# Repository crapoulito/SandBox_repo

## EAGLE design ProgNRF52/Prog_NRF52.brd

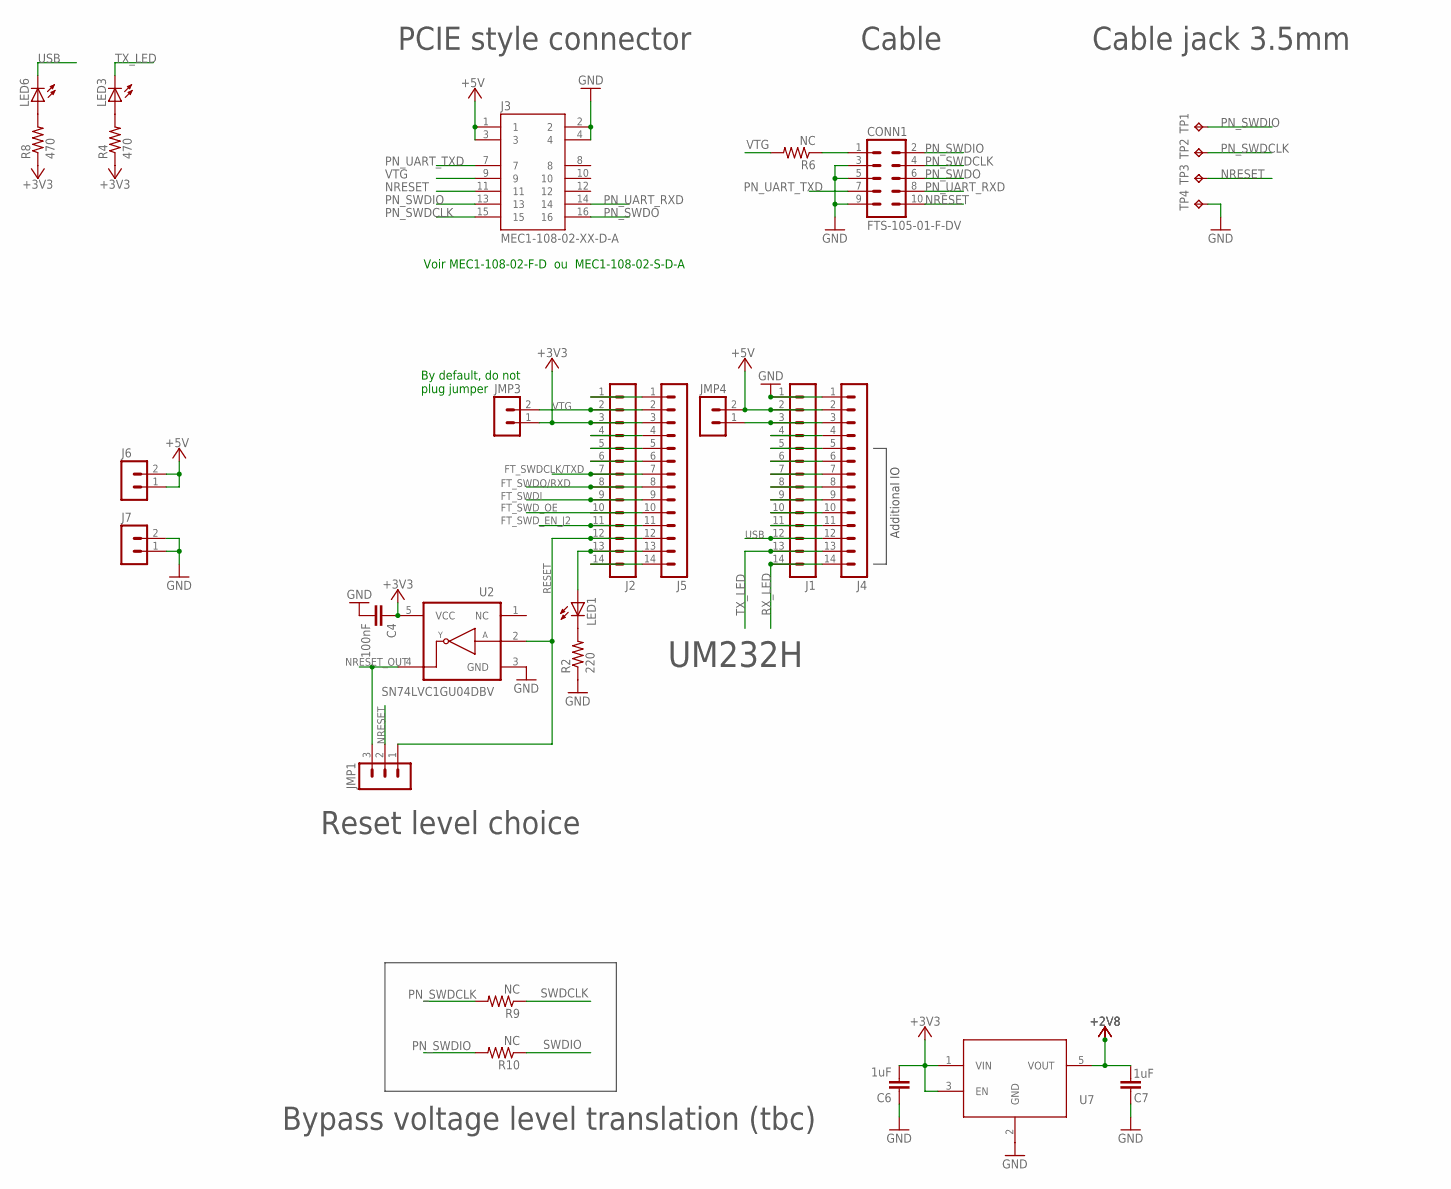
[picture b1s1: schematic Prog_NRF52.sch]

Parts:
C4: 100nF; C0603K
C6, C7: 1uF; C0603K
CONN1: FTS-105-01-F-DV
J1, J2, J4, J5: MA14-1
J3: MEC1-108-02-XX-D-A
J6, J7: MA02-1
JMP1: MA03-1
JMP3, JMP4: MA02-1
LED1, LED3, LED6: LEDCHIP-LED0603; CHIP-LED0603
R2: 220; R0603
R4, R8: 470; R0603
R6, R9, R10: NC; R0603
TP1, TP2, TP3, TP4: TPPAD1-13; P1-13
U2: SN74LVC1GU04DBV; SOT23-5
U7: NCP114ASN280T1G; SOT23-5

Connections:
+2V8: C7.2, U7.5 (VOUT)
+3V3: C4.1, C6.2, J2.3, J5.3, JMP3.1, R4.1, R8.1, U2.5 (VCC), U7.1 (VIN), U7.3 (EN)
+5V: J1.2, J3.1, J3.3, J4.2, J6.1, J6.2, JMP4.2
FT_SWDCLK/TXD: J2.7, J5.7
FT_SWDI: J2.9, J5.9
FT_SWDO/RXD: J2.8, J5.8
FT_SWD_EN_J2: J2.11, J5.11
FT_SWD_OE: J2.10, J5.10
GND: C4.2, C6.1, C7.1, CONN1.3, CONN1.5, CONN1.9, J1.1, J3.2, J3.4, J4.1, J7.1, J7.2, R2.1, TP4.TP, U2.3 (GND), U7.2 (GND)
unnamed: J1.3, J4.3, JMP4.1
unnamed: LED1.C, R2.2
unnamed: J2.13, J5.13, LED1.A
unnamed: LED3.A, R4.2
unnamed: J1.4, J4.4
unnamed: J1.5, J4.5
unnamed: J1.6, J4.6
unnamed: J1.7, J4.7
unnamed: J1.8, J4.8
unnamed: J1.9, J4.9
unnamed: J1.10, J4.10
unnamed: J1.11, J4.11
unnamed: LED6.A, R8.2
unnamed: J2.1, J5.1
unnamed: J2.4, J5.4
unnamed: J2.5, J5.5
unnamed: J2.6, J5.6
unnamed: J2.14, J5.14
unnamed: CONN1.1, R6.1
NRESET: CONN1.10, J3.11, JMP1.2, TP3.TP
NRESET_OUT: JMP1.3, U2.4 (Y)
PN_SWDCLK: CONN1.4, J3.15, R9.2, TP2.TP
PN_SWDIO: CONN1.2, J3.13, R10.2, TP1.TP
PN_SWDO: CONN1.6, J3.16
PN_UART_RXD: CONN1.8, J3.14
PN_UART_TXD: CONN1.7, J3.7
RESET: J2.12, J5.12, JMP1.1, U2.2 (A)
RX_LED: J1.14, J4.14
SWDCLK: R9.1
SWDIO: R10.1
TX_LED: J1.13, J4.13, LED3.C
USB: J1.12, J4.12, LED6.C
VTG: J2.2, J3.9, J5.2, JMP3.2, R6.2

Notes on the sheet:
Cable
UM232H
Additional IO
By default, do not plug jumper
Reset level choice
Voir MEC1-108-02-F-D ou MEC1-108-02-S-D-A
PCIE style connector
Cable jack 3.5mm
Bypass voltage level translation (tbc)

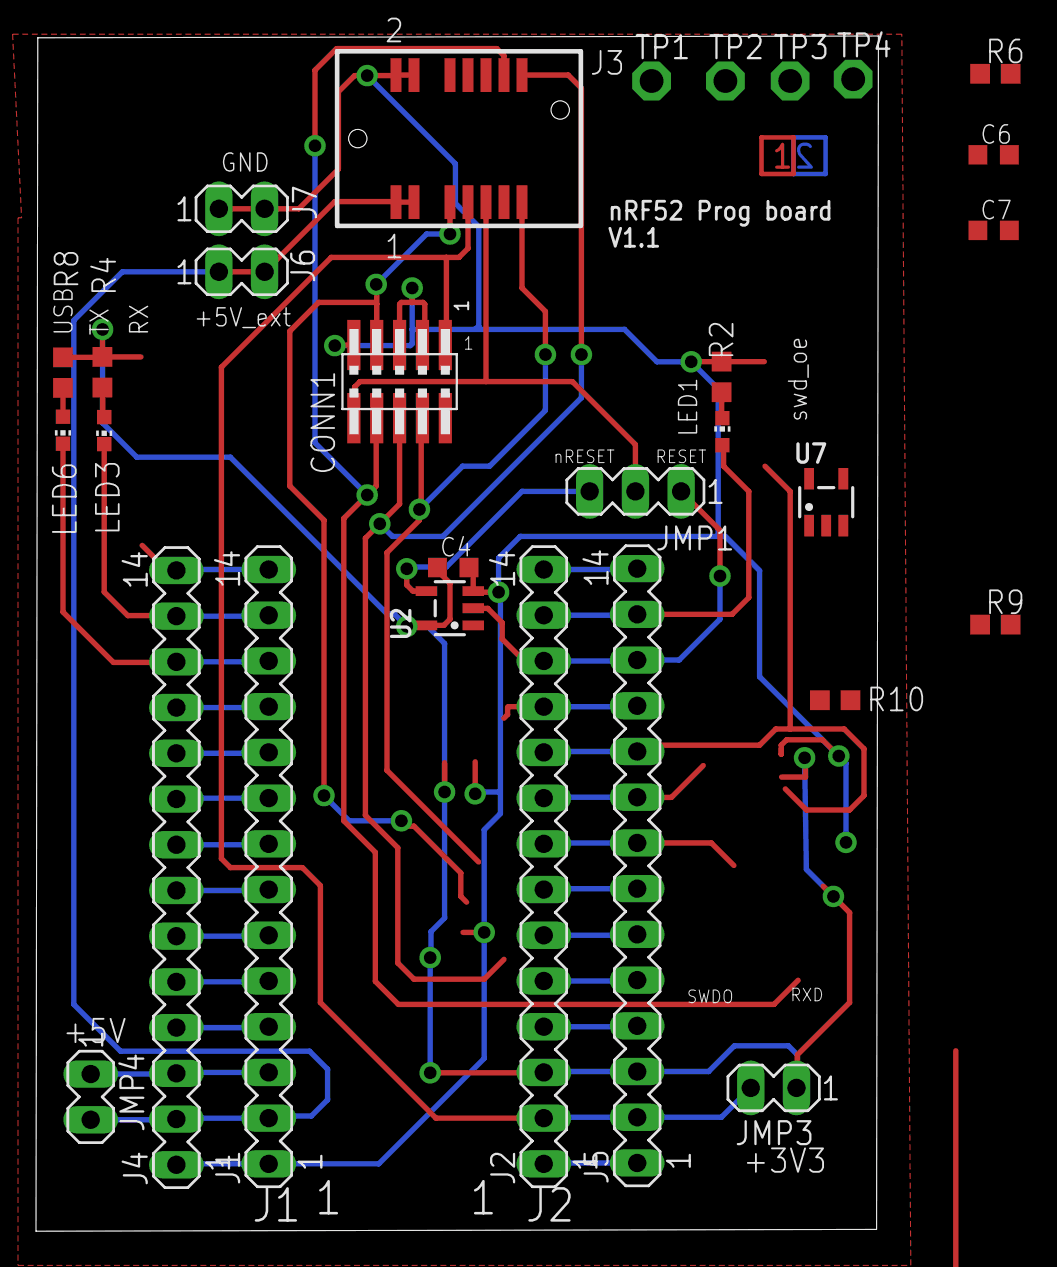
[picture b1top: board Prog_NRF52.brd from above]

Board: 2 copper layers, 46.8 x 66.4 mm, 29 parts (0 on the bottom side), 40 nets.

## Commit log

2018-10-03 Initial commit
    1st push
2018-10-03 Test specific modif
    Changing bom and comments
2018-10-03 Change layout
    Changing current layout
2018-10-03 update schematic comments
    update schematic and layout
2018-10-03 Suppress led on schematic
    Useless led where suppress
2018-10-03 Test : remove voltage translation unit
    Remove to test revory sch
2018-10-03 Wrong suppressing of logical gates
    Consider an error

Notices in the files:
parts and their libraries:
74LV: Copyright (C) 2008, Bob Starr
